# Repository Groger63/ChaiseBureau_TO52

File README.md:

# ChaiseBureau_TO52

TO52
Zamiati Nahil
Chambefort Quentin

Chaise de Bureau Connectée : Cahier des charges

Présentation

Le but du projet est de créer un siège connecté et intelligent s’intégrant dans un environnement d’objets connecté. Celui-ci a pour but de faciliter la vie de l’utilisateur en choisissant de manière automatique les réglages de position de confort.

Besoins & objectifs

Le siège doit être confortable.
Le siège doit pouvoir se régler de manière manuelle à l’aide de boutons physiques/interface à l’écran. (Application en réseau local)
Le siège doit pourvoir être contrôlé de manière automatique selon des paramètres utilisateurs (mémoire de position)
Le siège doit pouvoir s’intégrer dans un environnement d’objets connectés (assistant vocal, application bureau, etc…)
Le siège doit pouvoir détecter si une personne est assise dessus.
Le siège doit proposer des API de développement.
Le siège doit fonctionner sans fil.
Le siège doit pouvoir se connecter à un réseau wifi.

Contraintes du projet

Le siège doit être développé sur la base d’un siège passager de 406 coupé.

Difficultés envisagées

Choix du matériel : carte de programmation adéquate (Rpi, arduino ?) Composants électroniques (potentiomètres, rotary encoders ?), assistant vocal (Amazon Alexa, Google Home ?) etc…
Partie conception mécanique et adaptation de pièces sur le châssis du siège.
Découverte des API pour les différents assistants vocaux sur le marché. 
Résultats attendus

Le délivrable du projet sera le code source associé au développement, les divers plans de montage mécanique & électroniques, un mode d’emploi, ainsi que le siège en lui-même.

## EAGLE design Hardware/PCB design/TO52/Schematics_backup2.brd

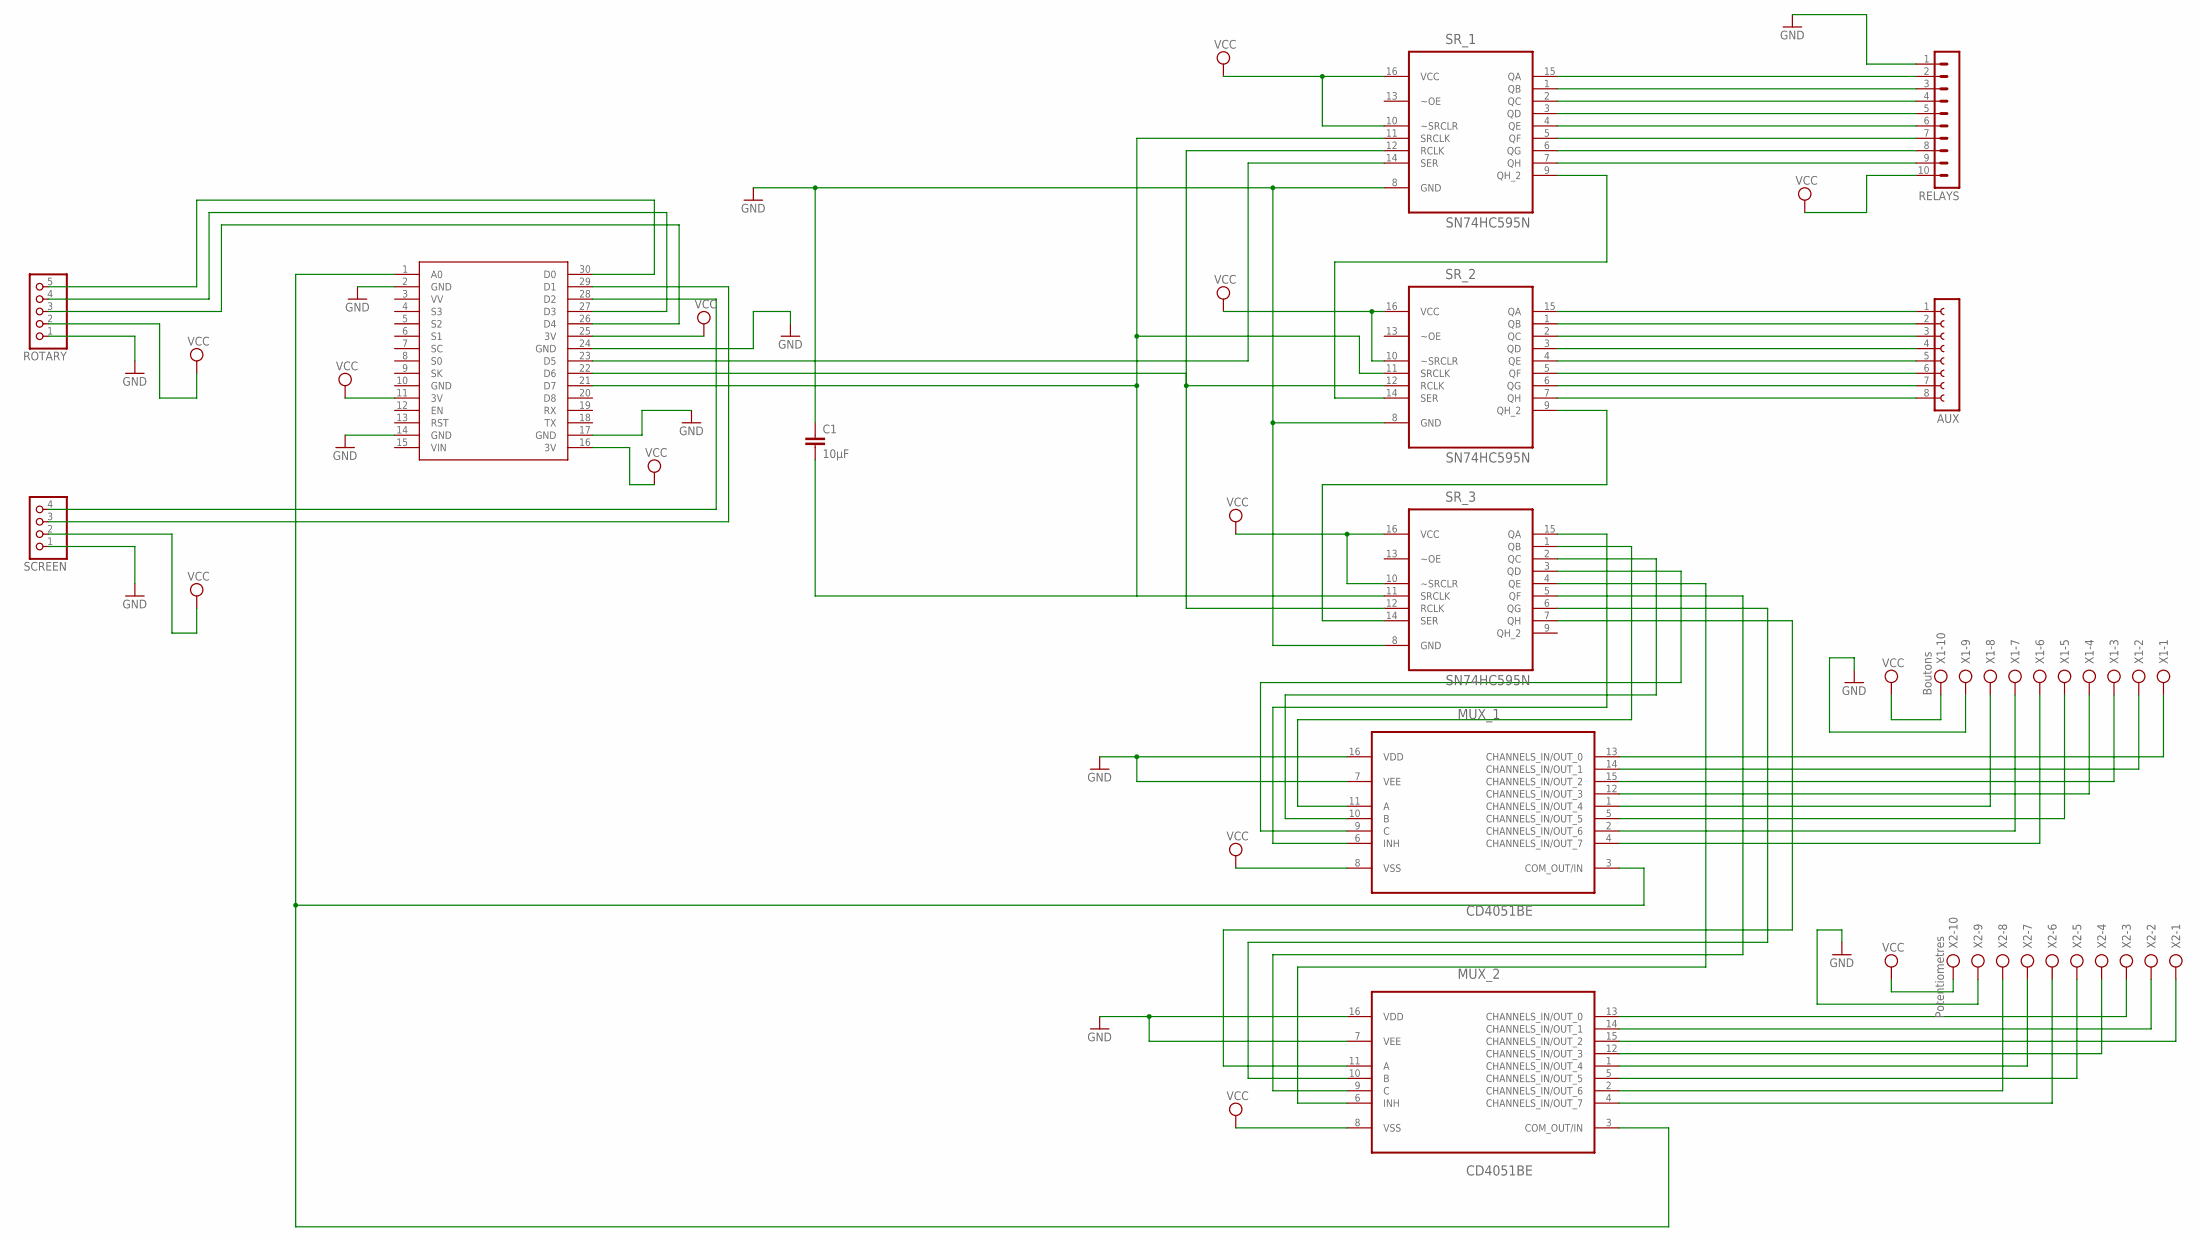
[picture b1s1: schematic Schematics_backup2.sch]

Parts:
AUX: FE08-1; FE08
C1: 10µF; C2.5-3
MUX_1, MUX_2: CD4051BE; DIP254P762X508-16
RELAYS: MA10-1W
ROTARY: PINHD-1X5; 1X05
SCREEN: PINHD-1X4; 1X04
SR_1, SR_2, SR_3: SN74HC595N; DIP254P762X508-16
U$1: NODEMCU
X1: Boutons; AK300/10
X2: Potentiometres; AK300/10

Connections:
GND: C1.1, MUX_1.7 (VEE), MUX_1.16 (VDD), MUX_2.7 (VEE), MUX_2.16 (VDD), RELAYS.1, ROTARY.1, SCREEN.1, SR_1.8 (GND), SR_2.8 (GND), SR_3.8 (GND), U$1.2 (GND), U$1.10 (GND), U$1.14 (GND), U$1.17 (GND), U$1.24 (GND), X1.9, X2.9
unnamed: RELAYS.2, SR_1.15 (QA)
unnamed: SR_1.14 (SER), U$1.23 (D5)
unnamed: SR_1.12 (RCLK), SR_2.12 (RCLK), SR_3.12 (RCLK), U$1.22 (D6)
unnamed: SR_2.9 (QH_2), SR_3.14 (SER)
unnamed: C1.2, SR_1.11 (SRCLK), SR_2.11 (SRCLK), SR_3.11 (SRCLK), U$1.21 (D7)
unnamed: RELAYS.3, SR_1.1 (QB)
unnamed: RELAYS.4, SR_1.2 (QC)
unnamed: RELAYS.5, SR_1.3 (QD)
unnamed: RELAYS.6, SR_1.4 (QE)
unnamed: RELAYS.7, SR_1.5 (QF)
unnamed: RELAYS.8, SR_1.6 (QG)
unnamed: RELAYS.9, SR_1.7 (QH)
unnamed: MUX_1.13 (CHANNELS_IN/OUT_0), X1.1
unnamed: MUX_1.14 (CHANNELS_IN/OUT_1), X1.2
unnamed: SR_1.9 (QH_2), SR_2.14 (SER)
unnamed: MUX_1.15 (CHANNELS_IN/OUT_2), X1.3
unnamed: MUX_1.12 (CHANNELS_IN/OUT_3), X1.4
unnamed: MUX_1.1 (CHANNELS_IN/OUT_4), X1.8
unnamed: MUX_1.5 (CHANNELS_IN/OUT_5), X1.5
unnamed: MUX_1.2 (CHANNELS_IN/OUT_6), X1.7
unnamed: MUX_1.4 (CHANNELS_IN/OUT_7), X1.6
unnamed: MUX_2.1 (CHANNELS_IN/OUT_4), X2.7
unnamed: MUX_2.2 (CHANNELS_IN/OUT_6), X2.8
unnamed: MUX_1.6 (INH), SR_3.15 (QA)
unnamed: MUX_1.11 (A), SR_3.1 (QB)
unnamed: MUX_1.10 (B), SR_3.2 (QC)
unnamed: MUX_1.9 (C), SR_3.3 (QD)
unnamed: MUX_2.6 (INH), SR_3.4 (QE)
unnamed: MUX_2.9 (C), SR_3.5 (QF)
unnamed: MUX_2.10 (B), SR_3.6 (QG)
unnamed: MUX_2.11 (A), SR_3.7 (QH)
unnamed: MUX_1.3 (COM_OUT/IN), MUX_2.3 (COM_OUT/IN), U$1.1 (A0)
unnamed: MUX_2.4 (CHANNELS_IN/OUT_7), X2.6
unnamed: MUX_2.5 (CHANNELS_IN/OUT_5), X2.5
unnamed: MUX_2.12 (CHANNELS_IN/OUT_3), X2.4
unnamed: MUX_2.15 (CHANNELS_IN/OUT_2), X2.1
unnamed: MUX_2.14 (CHANNELS_IN/OUT_1), X2.2
unnamed: MUX_2.13 (CHANNELS_IN/OUT_0), X2.3
unnamed: AUX.1, SR_2.15 (QA)
unnamed: AUX.2, SR_2.1 (QB)
unnamed: AUX.3, SR_2.2 (QC)
unnamed: AUX.4, SR_2.3 (QD)
unnamed: AUX.5, SR_2.4 (QE)
unnamed: AUX.6, SR_2.5 (QF)
unnamed: AUX.7, SR_2.6 (QG)
unnamed: AUX.8, SR_2.7 (QH)
unnamed: ROTARY.3, U$1.26 (D4)
unnamed: ROTARY.5, U$1.30 (D0)
unnamed: ROTARY.4, U$1.27 (D3)
unnamed: SCREEN.4, U$1.28 (D2)
unnamed: SCREEN.3, U$1.29 (D1)
VCC: MUX_1.8 (VSS), MUX_2.8 (VSS), RELAYS.10, ROTARY.2, SCREEN.2, SR_1.10 (~SRCLR), SR_1.16 (VCC), SR_2.10 (~SRCLR), SR_2.16 (VCC), SR_3.10 (~SRCLR), SR_3.16 (VCC), U$1.11 (3V), U$1.16 (3V), U$1.25 (3V), X1.10, X2.10

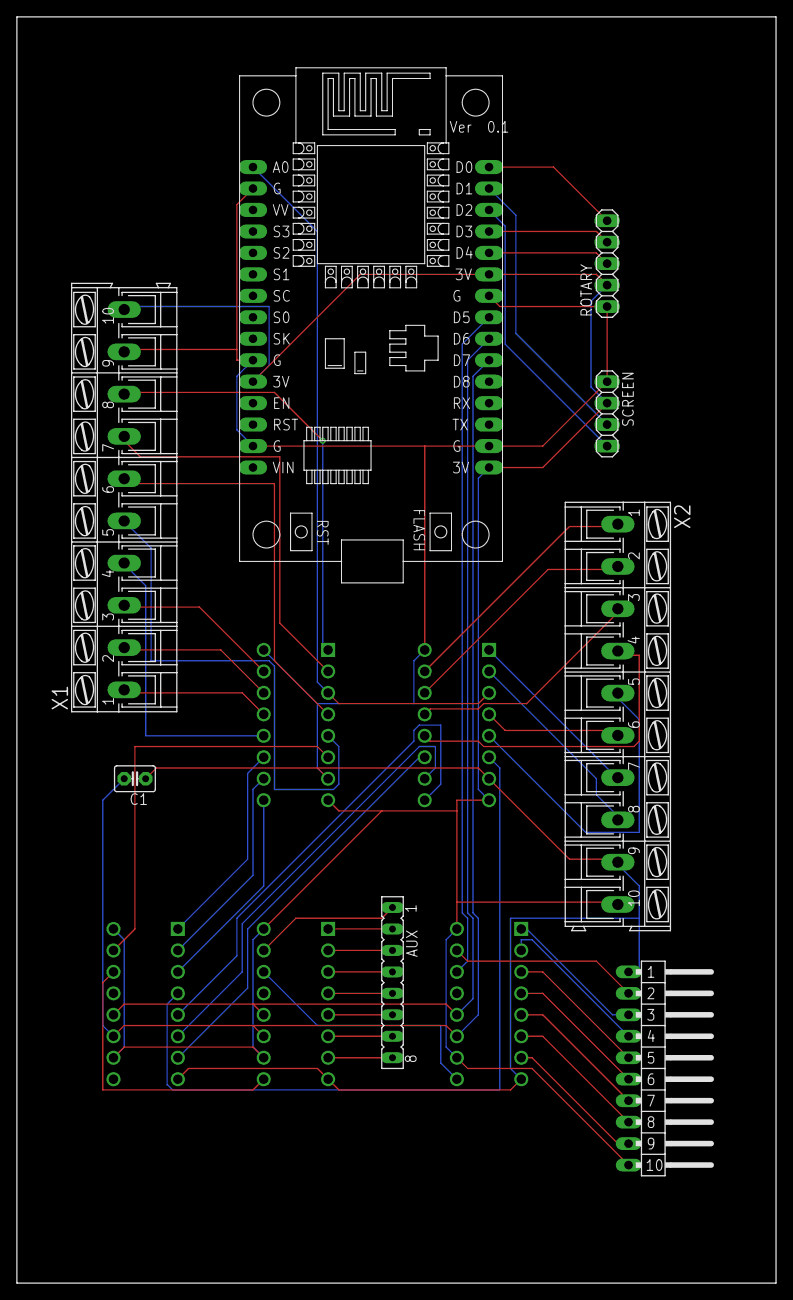
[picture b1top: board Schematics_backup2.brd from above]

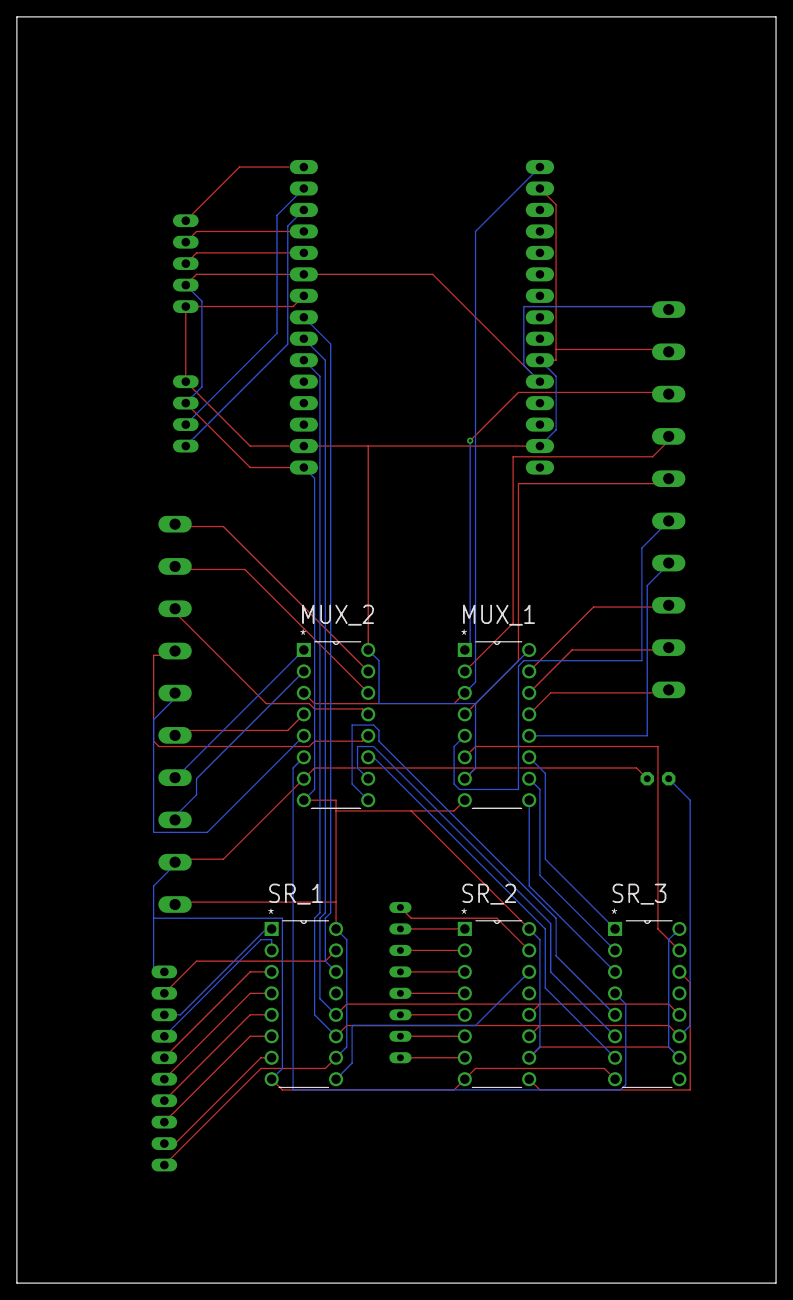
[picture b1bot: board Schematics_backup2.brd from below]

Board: 2 copper layers, 89.8 x 149.8 mm, 13 parts (5 on the bottom side), 53 nets.

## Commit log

2018-10-16 Mise à jour du cahier des charges
2018-10-16 Ajout de trucs
2018-10-16 Ajout du fichier doc pour les axes de travail
2018-10-23 2e partie de la réflexion
2018-10-25 test du regshift
2018-11-08 Avancé pas mal la partie Arduino Contrôle des moteurs avec le shiftreg Préparé le terrain pour d'autres trucs La classe Arduino String possède des soucis avec la librairie freertos...
2018-11-28 Portage du code vers nodeMCU
2018-12-28 Long commit : MAJ du code de nodeMCU Ajout des design du PCB et schéma électrique Ajout des pièces CATIA pour les adaptateurs des capteurs
2018-12-28 Ajout de la connexion wifi
2018-12-30 ajout de fonctions de connexion wifi
2018-12-30 MAJ des librairies moteurs pour avoir une position en %
2019-01-02 Nettoyage de l'arborescence
2019-01-02 Ajout du rapport
2019-01-02 Avancement du rapport
2019-01-04 MAJ rapport & ajout schéma electrique siege de base
2019-01-05 maj rapport
2019-01-07 Wifi fonctionnel
2019-01-11 Update général de code wifi
2019-01-14 Implémentation des menus wifi fonctionnelle
2019-01-14 Ajout de JEAN-SIEGEUI !
